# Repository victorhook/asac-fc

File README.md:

# ASAC FC

**A** **S**imple **A**nd **C**ool **F**light **C**ontroller (**ASAC FC**) is a completely open-source flight controller that can run on multiple microcontrollers such as:
- rp2040
- rp2350

## Project goals
- [ ] Build a drone with rp2040 devboard + external IMU
- [ ] Build a drone with rp2350 devboard + external IMU
- [ ] Add Stabilize flight mode
- [ ] Add Althold flight mode (requires barometer)
- [ ] Add support for SD card logging
- [ ] UI To configure board
- [X] Separate HAL to build for different platforms (rp2040, sitl etc)

What should be configurable, and what should be built-in to firmware?
### Built-in
Must still be able to boot OK without any of these

### Configurable
- Barometer
- IMU
- RC receiver
- Motor order
- FC orientation

---

TODO: THIS GIF [ASAC Takeoff](docs/asac_takeoff.gif)

## Why rp2040?
It's an incredibly cheap microcontroller that is quite powerful (up to 133 MHz), contains two cores, programmable I/O pins (PIO), seems to ignore the global silicon shortage and has an extensive C/C++ SDK.

## Iteration 2

For the second iteration of the flight controller I designed a PCB in FreeCad, ordered the pcb and components with SMD assembly for the top layer, and soldered the bottom layer myself. All cad files of this can be found in [kicad/asac-fc-rev-b](kicad/asac-fc-rev-b). Schematic can also be found at [documents/asac-fc-rev-b.pdf](documents/asac-fc-rev-b.pdf).
Some nice features of the flight controller PCB are:

- **rp2040** - Flight controller (where asac runs)
- **BMI270** - IMU, using SPI, which allows faster readings than the MPU-6050 which was used for iteration 1.
- **USB-C** - More modern, right? :)
- **Individual ESC solder pads** - Connection for individual ESCs. While most flight stacks today use an 4-in-1 ESC, I decided to keep it simple and use individual ESCs for now.
- **Battery solder pads**

## Iteration 1

The first iteration of *asac fc* was done with development boards, before designing a custom PCB. This is to make a proof of concept, and serves as a sanity check to show that it's possible :). The main components are:
- **Raspberry pi pico** - Flight controller (where asac runs)
- **MPU6050** - IMU
- **FS-a8s** - Radio receiver (Flysky, outputs IBUS)
- **xsd7a ESC** - ESCs (Single motor ESCs, so 4 in total)
- **Frame** - Custom designed, 3D-printed in PLA.

I created a simple power distribution board (brown part, at the bottom of the drone in the picture below), where the battery is connected to. Each ESC as well as the pico and the receiver gets its power from this board. The ESCs are then connected to GPIOs on the pico.

After some manual (headless) flights, I decided to add an analog camera together with a VTX I had laying around. This way, we can fly some FPV with the pico!

## Features

### Sensors
- [X] IMU
- [ ] GPS
- [ ] Barometer (altitude estimation)
- [ ] Lidar or other distance sensor

### Receiver protocols
- [X] IBUS
- [ ] SBUS
- [ ] Frsky
- [ ] CSRF

### Telemetry
- [ ] Any

### Flight modes
- [X] Acro (attitude rate, aka free-style)
- [ ] Any other stabilizing mode

### ESC Protocols

- [X] PWM (50 hz)
- [X] Oneshot125, utilizing rp2040s PIO block
- [X] Oneshot42, utilizing rp2040s PIO block
- [ ] Multishot
- [ ] Dshot150
- [ ] Dshot300
- [ ] Dshot600
- [ ] Dshot1200
- [ ] ProShot

## From receiver input to motor outputs

In order to set the correct speeds for each motor, several steps must be taken. The steps described below is how it's done for *asac fc*. Note that this is for acro mode only (freestyle, using only gyro rates from IMU).

1. Read gyro rates from IMU
2. Remove bias from gyro reading
3. Filter gyro reading
4. Read receiver input
5. Convert receiver stick inputs to desired gyro rates. This is a mapping from eg. 1000-2000 -> -500 to 500 deg/s.
6. Give the *desired* rates together with the *measured* rates to PID controller that uses PID parameters to calculate adjustment values.
7. Give output from PID controller to motor mixer to get commands for each motor.
8. Send the motor outputs to the ESC(s).

## RTOS
*asac fc* uses a very simple RTOS called [vsrtos](https://github.com/victorhook/vsrtos), that uses a priority based non-preemptive scheduling technique to run tasks. While this rtos is quite immature, it works just fine for this application, since *asac fc* doesn't have that many tasks yet.

## Motor mixing

The motor mixer is responsible for deciding which motor should spin and how much. *asac fc* uses the default motor numbers like in the image below, which is the same as the default for betaflight.

The default motor mix is:

| Motor | Throttle | Roll | Pitch | Yaw |
| --- | --- | --- | --- | --- |
| 1 | 1 | -1 | 1  | -1 |
| 2 | 1 | -1 | -1 | 1  |
| 3 | 1 | 1  | 1  | 1 |
| 4 | 1 | 1  | -1 | -1  |

## Flashing

You can flash the pico through in three different ways:
1. Through USB, when it's connected as a USB device (press down button while powering the pico)
2. Through serial USB by utilizing the picotool:
   `picotool load -f target.uf2 && picotool reboot -f`
    This works if uart 0 is mapped to USB:
    ```
    pico_enable_stdio_uart(asac-fc 0)
    pico_enable_stdio_usb(asac-fc 1)
    ```
    The command above first flashes the target `uf2` file to the pico by forcing it into BOOTSEL mode. We then reset the pico with `picotool reboot -f`. The flag `-f` is crucial here, since it allows us to load and reboot it without being in BOOTSEL mode already. I think it accomplishes this by changing the baud rate of the connection, which forces the pico to BOOTSEL mode, but I am not 100% sure.
3. SWD using debugger/another pico.

## Available build defines

There are several parameters that can be defined on build-time to configure the firmware. All of the defines can also be found in the `CMakeLists.txt` These includes:

| Define | Description |
| --- | --- |
| USE_DEFAULT_SETTINGS | If defined, asac will use default settings and write them to flash. Note that this will erase any previous settings that were stored in flash. This can be useful when using the flight controller for the first time, or updating the data structure of the flash. |
| LINUX | If defined, the firmware is built to be run on a linux machine and *not* for rp2040. This can be useful if you want to run unit tests on certain parts of code, or simulate fc. |
| RP2040 | Used by vsrtos. Do not change |

## Resources
- [Embedded Programming for Quadcopters](https://www.youtube.com/watch?v=CHSYgLfhwUo&ab_channel=Code%26Supply)
- [Motor mixing](https://oscarliang.com/custom-motor-output-mix-quadcopter/)

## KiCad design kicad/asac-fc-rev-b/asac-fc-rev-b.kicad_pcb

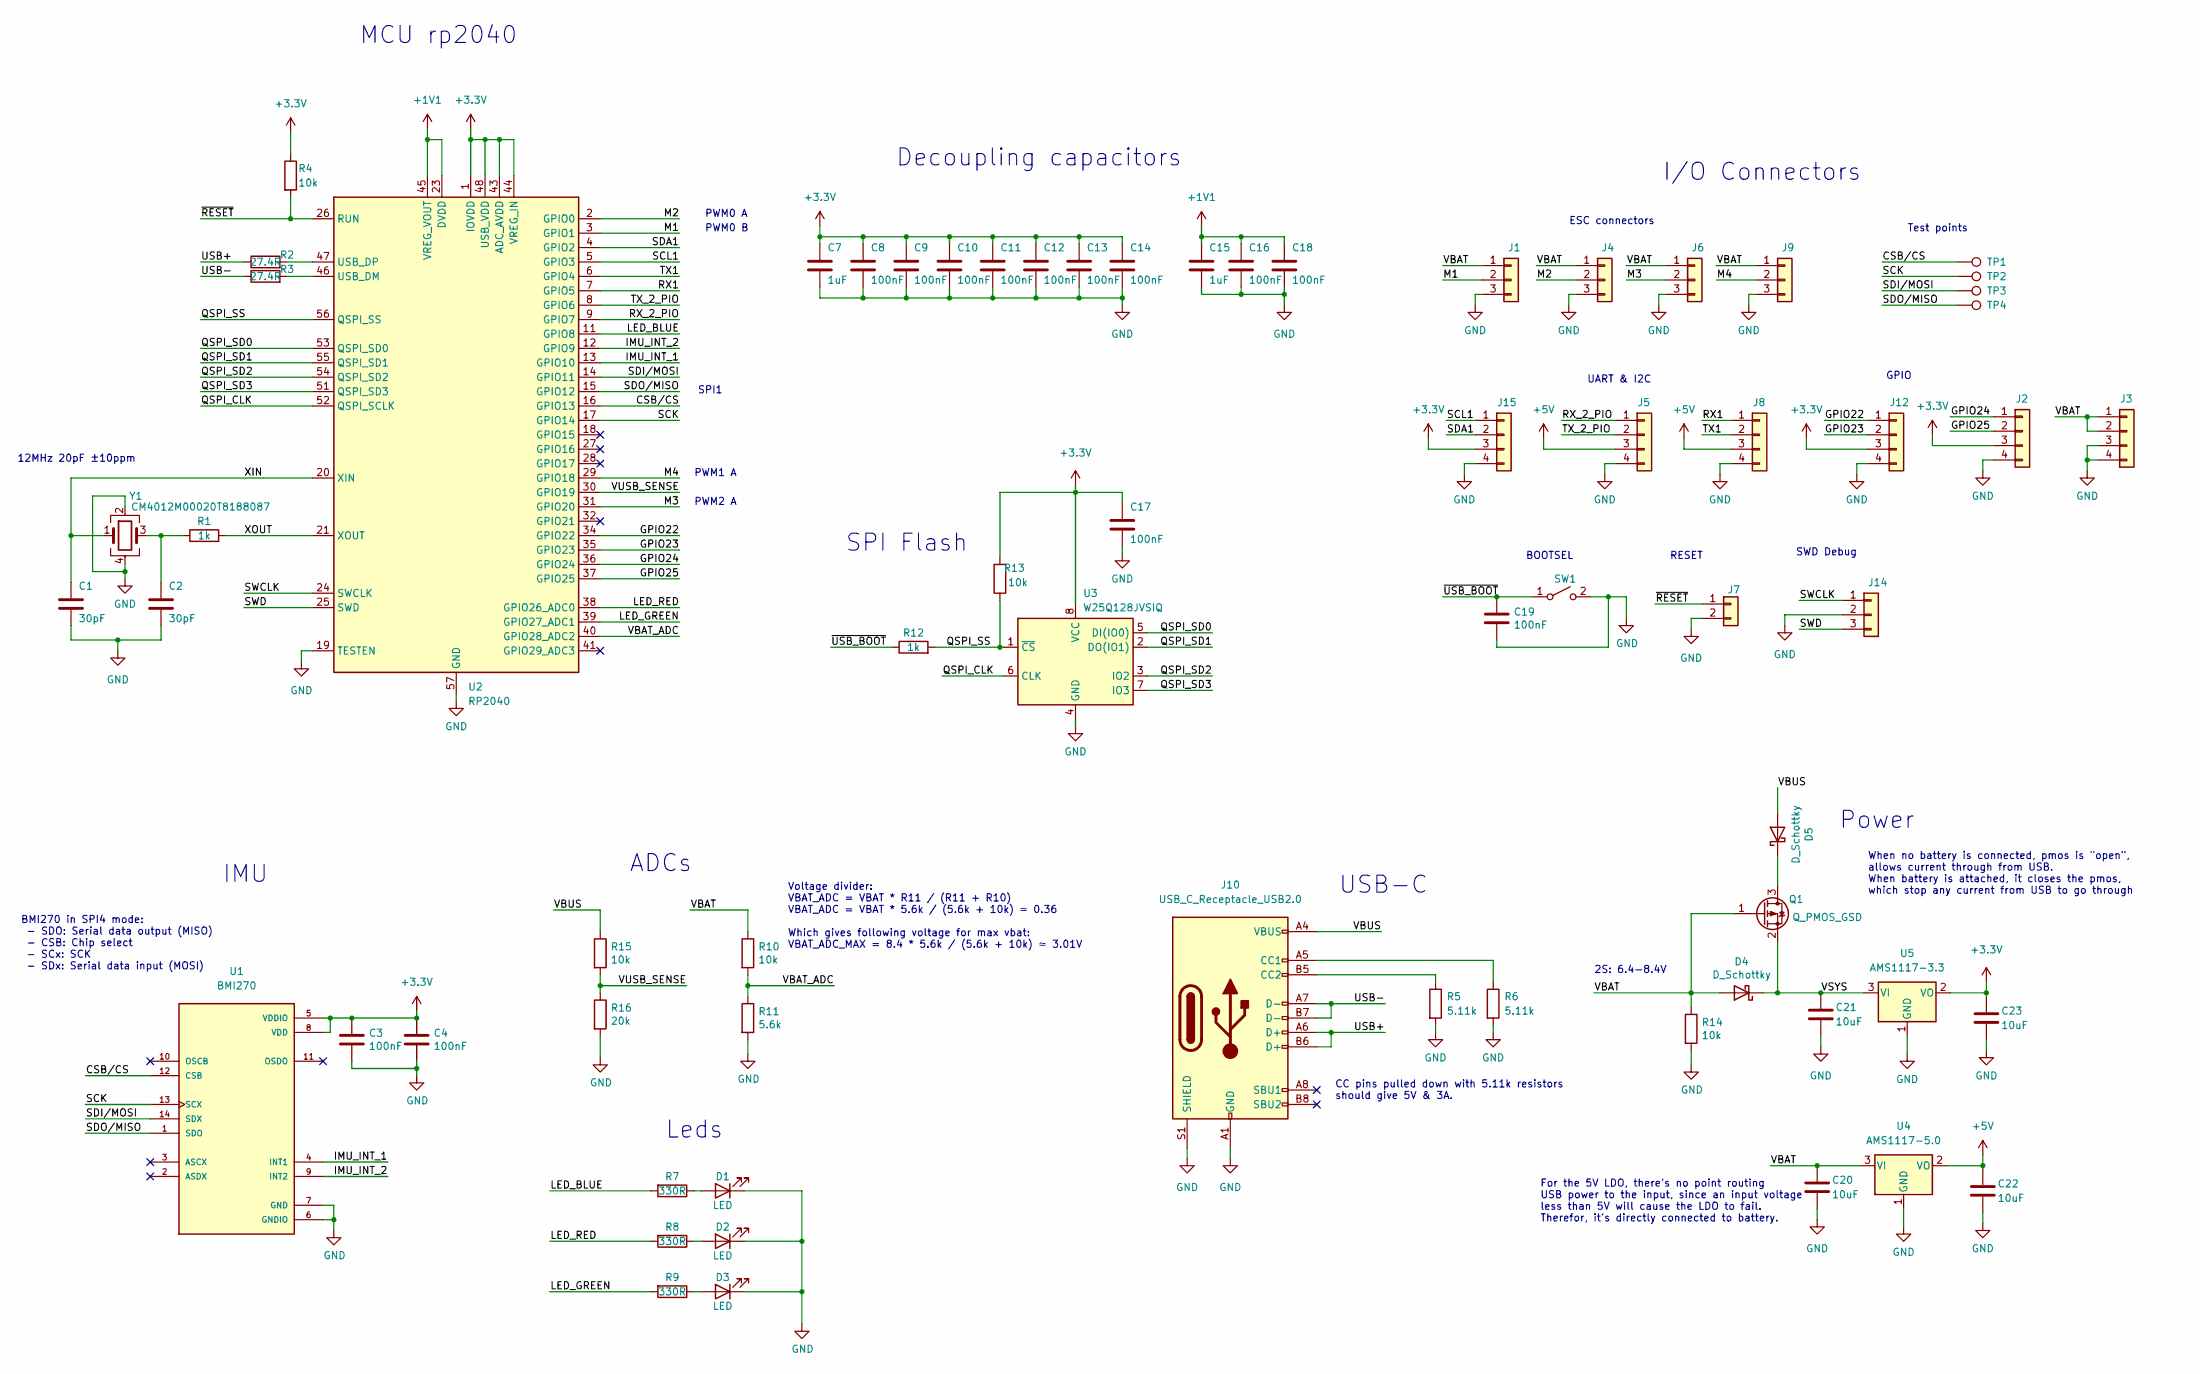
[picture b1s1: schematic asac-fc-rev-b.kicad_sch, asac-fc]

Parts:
C1, C2: 30pF; C_0402_1005Metric
C3, C4, C8, C9, C10, C11, C12, C13, C14, C16, C17, C18, C19: 100nF; C_0402_1005Metric
C7, C15: 1uF; C_0402_1005Metric
C20, C21, C22, C23: 10uF; C_0805_2012Metric
D1, D2, D3: LED; LED_0603_no_outline
D4, D5: D_Schottky; D_SOD-123
J1, J4, J6, J9: Conn_01x03; Conn_01x03_2big_1small
J2, J3, J5, J8, J12, J15: Conn_01x04; Conn_01x04_fpv
J7: Conn_01x02; Conn_01x02_small
J10: USB_C_Receptacle_USB2.0; USB-SMD_GT-USB-7010AN
J14: Conn_01x03; PinHeader_1x03_P1.27mm_Vertical_no_silk_smd
Q1: Q_PMOS_GSD; SOT-23
R1, R12: 1k; R_0402_1005Metric
R2, R3: 27.4R; R_0402_1005Metric
R4, R10, R13, R14, R15: 10k; R_0402_1005Metric
R5, R6: 5.11k; R_0402_1005Metric
R7, R8, R9: 330R; R_0402_1005Metric
R11: 5.6k; R_0402_1005Metric
R16: 20k; R_0402_1005Metric
SW1: SW_SPST; SW-SMD_TS-1086EV-16
TP1, TP2, TP3, TP4: TestPoint; TP_0.7mm
U1: BMI270
U2: RP2040; QFN-56-1EP_7x7mm_P0.4mm_EP3.2x3.2mm
U3: W25Q128JVSIQ; SOIC-8_5.23x5.23mm_P1.27mm
U4: AMS1117-5.0; SOT-223-3_TabPin2
U5: AMS1117-3.3; SOT-223-3_TabPin2
Y1: CM4012M00020T8188087; Crystal_SMD_2520-4Pin_2.5x2.0mm

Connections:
+1V1: C15.1, C16.1, C18.1, U2.23 (DVDD), U2.45 (VREG_VOUT), U2.50 (DVDD)
+3.3V: C3.1, C4.1, C7.1, C8.1, C9.1, C10.1, C11.1, C12.1, C13.1, C14.1, C17.1, C23.1, J2.3, J12.3, J15.3, R4.1, R13.2, U1.5 (VDDIO), U1.8 (VDD), U2.1 (IOVDD), U2.10 (IOVDD), U2.22 (IOVDD), U2.33 (IOVDD), U2.42 (IOVDD), U2.43 (ADC_AVDD), U2.44 (VREG_IN), U2.48 (USB_VDD), U2.49 (IOVDD), U3.8 (VCC), U5.2 (VO)
+5V: C22.1, J5.3, J8.3, U4.2 (VO)
/CSB/CS: TP1.1, U1.12 (CSB), U2.16 (GPIO13)
/GPIO22: J12.1, U2.34 (GPIO22)
/GPIO23: J12.2, U2.35 (GPIO23)
/GPIO24: J2.1, U2.36 (GPIO24)
/GPIO25: J2.2, U2.37 (GPIO25)
/IMU_INT_1: U1.4 (INT1), U2.13 (GPIO10)
/IMU_INT_2: U1.9 (INT2), U2.12 (GPIO9)
/LED_BLUE: R7.2, U2.11 (GPIO8)
/LED_GREEN: R9.2, U2.39 (GPIO27_ADC1)
/LED_RED: R8.2, U2.38 (GPIO26_ADC0)
/M1: J1.2, U2.3 (GPIO1)
/M2: J4.2, U2.2 (GPIO0)
/M3: J6.2, U2.31 (GPIO20)
/M4: J9.2, U2.29 (GPIO18)
/QSPI_CLK: U2.52 (QSPI_SCLK), U3.6 (CLK)
/QSPI_SD0: U2.53 (QSPI_SD0), U3.5 (DI(IO0))
/QSPI_SD1: U2.55 (QSPI_SD1), U3.2 (DO(IO1))
/QSPI_SD2: U2.54 (QSPI_SD2), U3.3 (IO2)
/QSPI_SD3: U2.51 (QSPI_SD3), U3.7 (IO3)
/QSPI_SS: R12.2, R13.1, U2.56 (QSPI_SS), U3.1 (~CS)
/RX1: J8.1, U2.7 (GPIO5)
/RX_2_PIO: J5.1, U2.9 (GPIO7)
/SCK: TP2.1, U1.13 (SCX), U2.17 (GPIO14)
/SCL1: J15.1, U2.5 (GPIO3)
/SDA1: J15.2, U2.4 (GPIO2)
/SDI/MOSI: TP3.1, U1.14 (SDX), U2.14 (GPIO11)
/SDO/MISO: TP4.1, U1.1 (SDO), U2.15 (GPIO12)
/SWCLK: J14.1, U2.24 (SWCLK)
/SWD: J14.3, U2.25 (SWD)
/TX1: J8.2, U2.6 (GPIO4)
/TX_2_PIO: J5.2, U2.8 (GPIO6)
/USB+: J10.A6 (D+), J10.B6 (D+), R2.1
/USB-: J10.A7 (D-), J10.B7 (D-), R3.1
/VBAT: C20.1, D4.2 (A), J1.1, J3.1, J3.2, J4.1, J6.1, J9.1, Q1.1 (G), R10.1, R14.1, U4.3 (VI)
/VBAT_ADC: R10.2, R11.1, U2.40 (GPIO28_ADC2)
/VBUS: D5.2 (A), J10.A4 (VBUS), J10.A9 (VBUS), J10.B4 (VBUS), J10.B9 (VBUS), R15.1
/VSYS: C21.1, D4.1 (K), Q1.2 (S), U5.3 (VI)
/VUSB_SENSE: R15.2, R16.1, U2.30 (GPIO19)
/XIN: C1.1, U2.20 (XIN), Y1.1
/XOUT: R1.2, U2.21 (XOUT)
/~RESET: J7.1, R4.2, U2.26 (RUN)
/~USB_BOOT: C19.1, R12.1, SW1.1 (A)
GND: C1.2, C2.2, C3.2, C4.2, C7.2, C8.2, C9.2, C10.2, C11.2, C12.2, C13.2, C14.2, C15.2, C16.2, C17.2, C18.2, C19.2, C20.2, C21.2, C22.2, C23.2, D1.1 (K), D2.1 (K), D3.1 (K), J1.3, J2.4, J3.3, J3.4, J4.3, J5.4, J6.3, J7.2, J8.4, J9.3, J10.A1 (GND), J10.A12 (GND), J10.B1 (GND), J10.B12 (GND), J10.S1 (SHIELD), J12.4, J14.2, J15.4, R5.2, R6.2, R11.2, R14.2, R16.2, SW1.2 (B), U1.6 (GNDIO), U1.7 (GND), U2.19 (TESTEN), U2.57 (GND), U3.4 (GND), U4.1 (GND), U5.1 (GND), Y1.2, Y1.4
unnamed: C2.1, R1.1, Y1.3
unnamed: D1.2 (A), R7.1
unnamed: D2.2 (A), R8.1
unnamed: D3.2 (A), R9.1
unnamed: D5.1 (K), Q1.3 (D)
unnamed: J10.A5 (CC1), R6.1
unnamed: J10.B5 (CC2), R5.1
unnamed: R2.2, U2.47 (USB_DP)
unnamed: R3.2, U2.46 (USB_DM)

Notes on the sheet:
Power
2S: 6.4-8.4V
MCU rp2040
BOOTSEL
Leds
UART & I2C
CC pins pulled down with 5.11k resistors should give 5V & 3A.
12MHz 20pF ±10ppm
PWM2 A
SPI Flash
SWD Debug
Test points
USB-C
ESC connectors
When no battery is connected, pmos is "open", allows current through from USB. When battery is attached, it closes the pmos, which stop any current from USB to go through
PWM1 A
Voltage divider: VBAT_ADC = VBAT * R11 / (R11 + R10) VBAT_ADC = VBAT * 5.6k / (5.6k + 10k) ≃ 0.36 Which gives following voltage for max vbat: VBAT_ADC_MAX = 8.4 * 5.6k / (5.6k + 10k) ≃ 3.01V
Decoupling capacitors
I/O Connectors
PWM0 A
SPI1
PWM0 B
For the 5V LDO, there's no point routing USB power to the input, since an input voltage less than 5V will cause the LDO to fail. Therefor, it's directly connected to battery.
BMI270 in SPI4 mode: - SDO: Serial data output (MISO) - CSB: Chip select - SCx: SCK - SDx: Serial data input (MOSI)
ADCs
GPIO
RESET
IMU

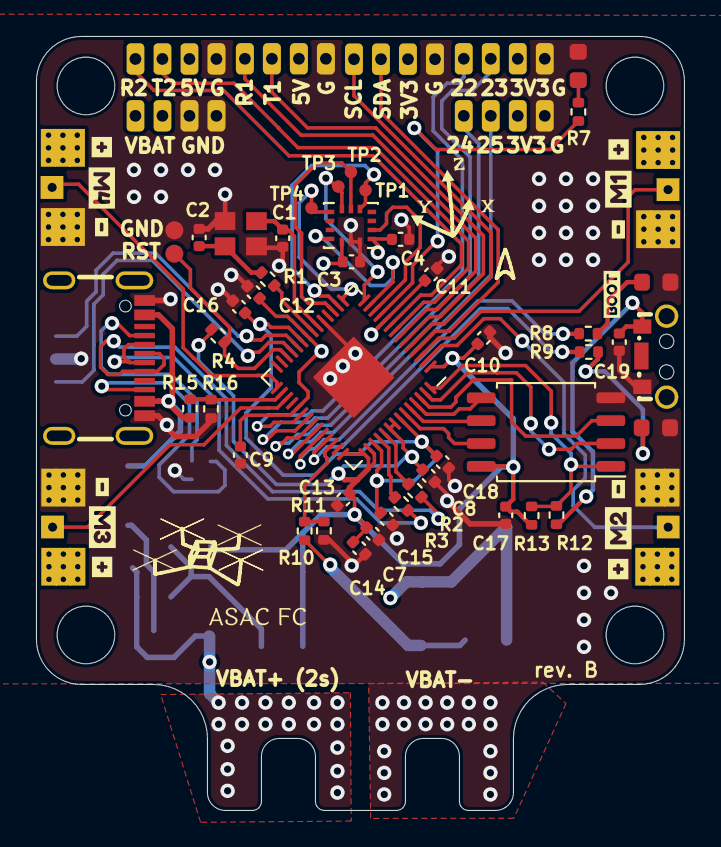
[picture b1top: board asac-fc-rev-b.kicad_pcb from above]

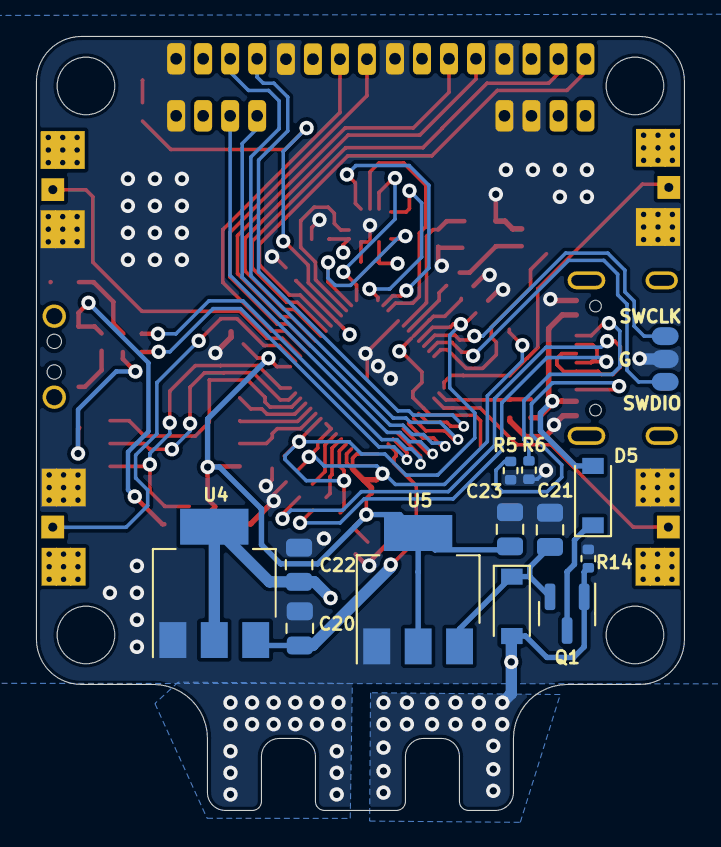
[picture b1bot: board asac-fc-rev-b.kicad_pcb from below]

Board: 4 copper layers, 36.0 x 43.0 mm, 80 parts (13 on the bottom side), 55 nets.

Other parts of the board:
kibuzzard-647F08DD, kibuzzard-647F08DD#2: G***; kibuzzard-647F08DD
kibuzzard-647F08EC, kibuzzard-647F08EC#2: G***; kibuzzard-647F08EC
kibuzzard-647F08F4: G***; kibuzzard-647F08F4
kibuzzard-647F09B6: G***; kibuzzard-647F09B6
kibuzzard-647F09BC: G***; kibuzzard-647F09BC
kibuzzard-647F096A, kibuzzard-647F096A#2: G***; kibuzzard-647F096A
kibuzzard-647F0963: G***; kibuzzard-647F0963
kibuzzard-647F0971, kibuzzard-647F0971#2: G***; kibuzzard-647F0971
kibuzzard-640905D0: G***; kibuzzard-640905D0

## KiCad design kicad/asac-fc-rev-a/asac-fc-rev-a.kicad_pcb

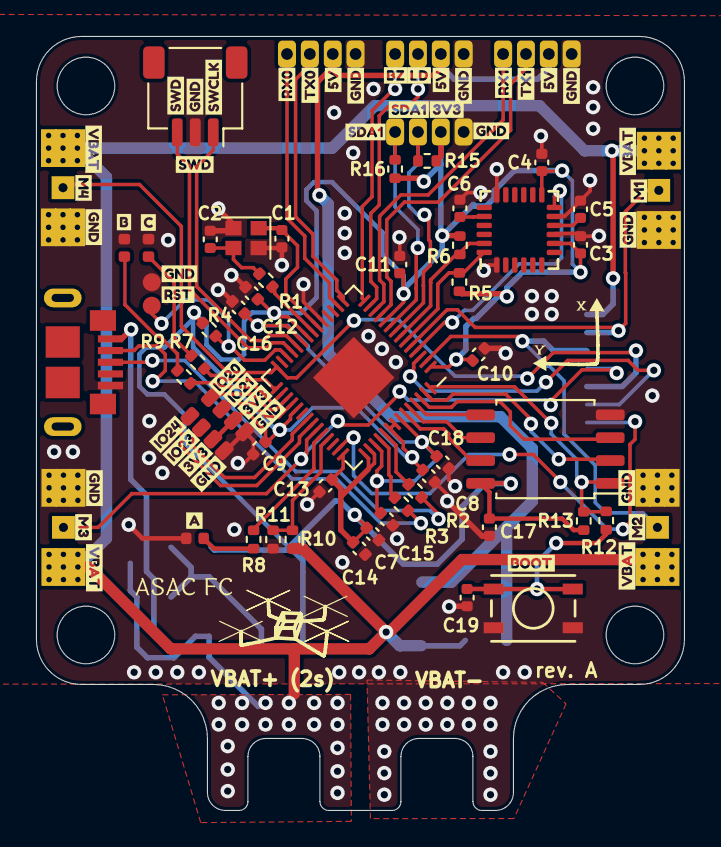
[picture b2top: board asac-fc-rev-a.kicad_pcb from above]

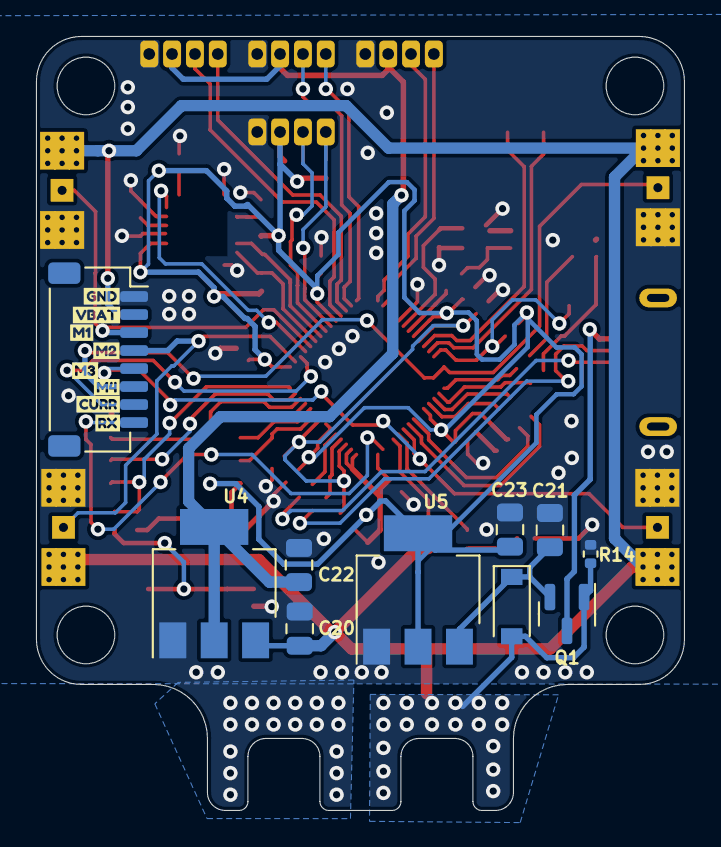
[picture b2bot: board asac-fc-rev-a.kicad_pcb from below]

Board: 2 copper layers, 36.0 x 43.0 mm, 119 parts (18 on the bottom side), 54 nets.

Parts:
C1, C2: 7pF; C_0402_1005Metric
C3, C4, C5, C8, C9, C10, C11, C12, C13, C14, C16, C17, C18: 0.1uF; C_0402_1005Metric
C6: 2.2nF; C_0402_1005Metric
C7, C15: 1uF; C_0402_1005Metric
C19: 100nF; C_0402_1005Metric
C20, C21, C22, C23: 10uF; C_0805_2012Metric
D1, D2, D3: LED; LED_0402_1005Metric_No_silk_dot
D4: D_Schottky; D_SOD-123
J1, J4, J6, J9: Conn_01x03; Conn_01x03_2big_1small
J2, J12: Conn_01x04; Conn_01x04_fpv_smd
J3: USB3075-30-A; USB3075-30-A_No_silk
J5, J8, J10, J15: Conn_01x04; Conn_01x04_fpv
J7: Conn_01x02; Conn_01x02_small
J11: Conn_01x08; JST_SH_SM08B-SRSS-TB_1x08-1MP_P1.00mm_Horizontal
J14: Conn_01x03; JST_SH_SM03B-SRSS-TB_1x03-1MP_P1.00mm_Horizontal
Q1: Q_PMOS_GSD; SOT-23
R1, R12: 1k; R_0402_1005Metric
R2, R3: 27.4; R_0402_1005Metric
R4, R10, R13, R14: 10k; R_0402_1005Metric
R5, R6, R15, R16: 2.2k; R_0402_1005Metric
R7, R8, R9: 330; R_0402_1005Metric
R11: 5.6k; R_0402_1005Metric
SW1: BOOT; PTS815
U1: MPU-6050; InvenSense_QFN-24_4x4mm_P0.5mm
U2: RP2040; QFN-56-1EP_7x7mm_P0.4mm_EP3.2x3.2mm
U3: W25Q128JVS; SOIC-8_5.23x5.23mm_P1.27mm
U4: AMS1117-5.0; SOT-223-3_TabPin2
U5: AMS1117-3.3; SOT-223-3_TabPin2
Y1: Crystal_GND24; Crystal_SMD_2016-4Pin_2.0x1.6mm
kibuzzard-6408FA6D, kibuzzard-6408FA6D#2, kibuzzard-6408FA6D#3, kibuzzard-6408FA6D#4: G***; kibuzzard-6408FA6D
kibuzzard-6408FA39: G***; kibuzzard-6408FA39
kibuzzard-6408FA47: G***; kibuzzard-6408FA47
kibuzzard-6408FA74, kibuzzard-6408FA74#2, kibuzzard-6408FA74#3: G***; kibuzzard-6408FA74
kibuzzard-6408FAC1: G***; kibuzzard-6408FAC1
kibuzzard-6408FAC8: G***; kibuzzard-6408FAC8
kibuzzard-6408FB3B: G***; kibuzzard-6408FB3B
kibuzzard-6408FB51: G***; kibuzzard-6408FB51
kibuzzard-6408FBAE: G***; kibuzzard-6408FBAE
kibuzzard-6408FBBA: G***; kibuzzard-6408FBBA
kibuzzard-6408FC3B: G***; kibuzzard-6408FC3B
kibuzzard-6408FC28: G***; kibuzzard-6408FC28
kibuzzard-6408FC36: G***; kibuzzard-6408FC36
kibuzzard-6408FC56: G***; kibuzzard-6408FC56
kibuzzard-6408FD3E, kibuzzard-6408FD3E#2, kibuzzard-6408FD3E#3, kibuzzard-6408FD3E#4: G***; kibuzzard-6408FD3E
kibuzzard-6408FD16: G***; kibuzzard-6408FD16
kibuzzard-6408FD22, kibuzzard-6408FD22#2, kibuzzard-6408FD22#3, kibuzzard-6408FD22#4: G***; kibuzzard-6408FD22
kibuzzard-6408FDA0: G***; kibuzzard-6408FDA0
kibuzzard-6408FDC2: G***; kibuzzard-6408FDC2
kibuzzard-6408FDE1: G***; kibuzzard-6408FDE1
kibuzzard-64090C7A: G***; kibuzzard-64090C7A
kibuzzard-64090F7E: G***; kibuzzard-64090F7E
kibuzzard-64090F8A: G***; kibuzzard-64090F8A
kibuzzard-64090F8F: G***; kibuzzard-64090F8F
kibuzzard-64090F9C: G***; kibuzzard-64090F9C
kibuzzard-64090F56: G***; kibuzzard-64090F56
kibuzzard-64090F66: G***; kibuzzard-64090F66
kibuzzard-64090F74: G***; kibuzzard-64090F74
kibuzzard-64090F95: G***; kibuzzard-64090F95
kibuzzard-640900D1: G***; kibuzzard-640900D1
kibuzzard-640901D1: G***; kibuzzard-640901D1
kibuzzard-640901E3: G***; kibuzzard-640901E3
kibuzzard-640905D0: G***; kibuzzard-640905D0
kibuzzard-640910AE, kibuzzard-640910AE#2: G***; kibuzzard-640910AE
kibuzzard-640910C2: G***; kibuzzard-640910C2
kibuzzard-640911E9: G***; kibuzzard-640911E9
kibuzzard-640911EE: G***; kibuzzard-640911EE
kibuzzard-6409014C: G***; kibuzzard-6409014C
kibuzzard-6409115F: G***; kibuzzard-6409115F
kibuzzard-64090145: G***; kibuzzard-64090145
kibuzzard-64091195, kibuzzard-64091195#2: G***; kibuzzard-64091195

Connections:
+1V1: C15.1, C16.1, C18.1, U2.23 (DVDD), U2.45 (VREG_VOUT), U2.50 (DVDD)
+3.3V: C3.1, C4.1, C7.1, C8.1, C9.1, C10.1, C11.1, C12.1, C13.1, C14.1, C17.1, C23.1, J2.3, J12.3, J15.3, R4.1, R5.1, R6.1, R13.2, R15.1, R16.1, U1.8 (VDDIO), U1.13 (VDD), U2.1 (IOVDD), U2.10 (IOVDD), U2.22 (IOVDD), U2.33 (IOVDD), U2.42 (IOVDD), U2.43 (ADC_AVDD), U2.44 (VREG_IN), U2.48 (USB_VDD), U2.49 (IOVDD), U3.8 (VCC), U5.2 (VO)
+5V: C22.1, J5.3, J8.3, J10.3, U4.2 (VO)
/BUZZER: J10.1, U2.14 (GPIO11)
/CURR: J11.7, U2.3 (GPIO1)
/GPIO20: J12.1, U2.31 (GPIO20)
/GPIO21: J12.2, U2.32 (GPIO21)
/GPIO23: J2.2, U2.35 (GPIO23)
/GPIO24: J2.1, U2.36 (GPIO24)
/IMU_INTERRUPT: U1.12 (INT), U2.4 (GPIO2)
/LED: J10.2, U2.13 (GPIO10)
/LED_BLUE: R7.2, U2.29 (GPIO18)
/LED_GREEN: R9.2, U2.30 (GPIO19)
/LED_RED: R8.2, U2.38 (GPIO26_ADC0)
/M1: J1.2, J11.3, U2.5 (GPIO3)
/M2: J4.2, J11.4, U2.2 (GPIO0)
/M3: J6.2, J11.5, U2.37 (GPIO25)
/M4: J9.2, J11.6, U2.28 (GPIO17)
/QSPI_CLK: U2.52 (QSPI_SCLK), U3.6 (CLK)
/QSPI_SD0: U2.53 (QSPI_SD0), U3.5 (DI(IO0))
/QSPI_SD1: U2.55 (QSPI_SD1), U3.2 (DO(IO1))
/QSPI_SD2: U2.54 (QSPI_SD2), U3.3 (IO2)
/QSPI_SD3: U2.51 (QSPI_SD3), U3.7 (IO3)
/QSPI_SS: R12.2, R13.1, U2.56 (QSPI_SS), U3.1 (~CS)
/RX0: J5.1, U2.16 (GPIO13)
/RX1: J8.1, U2.12 (GPIO9)
/RX_ESC: J11.8, U2.41 (GPIO29_ADC3)
/SCL0: R6.2, U1.23 (SCL), U2.7 (GPIO5)
/SCL1: J15.1, R16.2, U2.9 (GPIO7)
/SDA0: R5.2, U1.24 (SDA), U2.6 (GPIO4)
/SDA1: J15.2, R15.2, U2.8 (GPIO6)
/SWCLK: J14.1, U2.24 (SWCLK)
/SWD: J14.3, U2.25 (SWD)
/TX0: J5.2, U2.15 (GPIO12)
/TX1: J8.2, U2.11 (GPIO8)
/USB+: J3.3 (D+), R2.1
/USB-: J3.2 (D-), R3.1
/VBAT: C20.1, D4.2 (A), J1.1, J4.1, J6.1, J9.1, J11.2, Q1.1 (G), R10.1, R14.1, U4.3 (VI)
/VBAT_ADC: R10.2, R11.1, U2.39 (GPIO27_ADC1)
/VBUS: J3.1 (VBUS), Q1.3 (D)
/XIN: C1.1, U2.20 (XIN), Y1.1
/XOUT: R1.2, U2.21 (XOUT)
/~RESET: J7.1, R4.2, U2.26 (RUN)
/~USB_BOOT: C19.1, R12.1, SW1.1, SW1.2
GND: C1.2, C2.2, C3.2, C4.2, C5.2, C6.2, C7.2, C8.2, C9.2, C10.2, C11.2, C12.2, C13.2, C14.2, C15.2, C16.2, C17.2, C18.2, C19.2, C20.2, C21.2, C22.2, C23.2, D1.1 (K), D2.1 (K), D3.1 (K), J1.3, J2.4, J3.5 (GND), J4.3, J5.4, J6.3, J7.2, J8.4, J9.3, J10.4, J11.1, J12.4, J14.2, J15.4, R11.2, R14.2, SW1.3 (K), SW1.4 (A), U1.1 (CLKIN), U1.9 (AD0), U1.11 (FSYNC), U1.18 (GND), U2.19 (TESTEN), U2.57 (GND), U3.4 (GND), U4.1 (GND), U5.1 (GND), Y1.2, Y1.4
unnamed: C2.1, R1.1, Y1.3
unnamed: C5.1, U1.10 (REGOUT)
unnamed: C6.1, U1.20 (CPOUT)
unnamed: C21.1, D4.1 (K), Q1.2 (S), U5.3 (VI)
unnamed: D1.2 (A), R7.1
unnamed: D2.2 (A), R8.1
unnamed: D3.2 (A), R9.1
unnamed: R2.2, U2.47 (USB_DP)
unnamed: R3.2, U2.46 (USB_DM)

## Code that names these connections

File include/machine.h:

#ifndef MACHINE_H
#define MACHINE_H


// Pin definitions for custom PCB - Revision B
// TODO: Incorrect motor names!!
// Motor MIXER M1 and M2 are swapped. The motor mixer uses betaflights
// motor mix!
// M1 in schematic and PCB is actually M2 according to motor mixer :)
// So M1 and M2 are swapped
//#define PIN_M1                 1
//#define PIN_M2                 0
#define PIN_M3                20
#define PIN_M4                18
#define PIN_M1                 0
#define PIN_M2                 1

#define PIN_VBAT_ADC          28
#define VBAT_ADC_INPUT_NUMBER  2

#define PIN_IMU_MOSI          11
#define PIN_IMU_MISO          12
#define PIN_IMU_CS            13
#define PIN_IMU_SCK           14
#define PIN_IMU_INTERRUPT_1   10
#define PIN_IMU_INTERRUPT_2    9
#define IMU_SPI_BUS           spi1

#define PIN_VUSB_SENSE        19

#define PIN_SDA1               2
#define PIN_SCL1               3

#define PIN_TX1                4
#define PIN_RX1                5
#define PIN_TX2_PIO            6
#define PIN_RX2_PIO            7

#define PIN_LED_BLUE           8
#define PIN_LED_GREEN          27
#define PIN_LED_RED            26

#define PIN_TELEMETRY_TX 0

// 16 MB
#define ASAC_FC_FLASH_SIZE        (16 * 1024 * 1024)


#endif

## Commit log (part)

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2023-03-10 Added first blog post (not done yet)
2023-03-15 - Created some base source code files. - Added cmake file to build. - Added vscode config files for intellisense etc.
2023-03-15 Added some datasheets
2023-03-15 Created and added rough start of some random tools
2023-03-27 Added some 3d models
2023-03-27 Added kicad pcb
2023-03-28 Modified vscode settings to make debugging with SWD work.
2023-03-30 - Added logic to motor mixer - Added init method for pid-controller - Added more logic to controller_update() (PID-loop main function)
2023-04-01 - Some general cleanup - Change motor API, - Added arm state - Added connected state - First (unstable) takeoff done!
2023-04-05 - Made controller variables public - Made PID variables public - Added debug pwm pin to motors - Changed type pid params to floats - Added timeout on i2c reading for mpu driver
2023-05-04 Started working on a gui to plot and display logging telemetry parameters
2023-05-06 - Added logic for handling states (log blocks) - Extended backend to fetch from actual flask server
2023-05-27 - Added packed attribute to log structs - Configured telemetry module and made it work. This was implemented with pio UART, seems to work pretty well, even with 921600 baudrate. - Added while loop to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
2023-05-28 - Added timer functions to asac_fc and fixed bug in them - Added data integrity protection to ibus module, by inspecting and validating the checksum. Also improved the state machine of the module. - 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
2023-05-31 First controlled take-off and flight, wehooo!! - Found CRUICAL reason why drone spun onctrollably around yaw axis, the Z from IMU was expected to be pointing DOWN according the the PID controller, bu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
2023-05-31 Some minor cleanup for most files
2023-06-04 - Removed reading acc data from imu to save reading time. - Cleaned up control update function. - Tuned PID params after flying, increased quite a bit - Made TELEMETRY_LOGGING define to enable/disabl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
2023-06-04 Improved README.md
2023-06-11 Added oneshot PIO implementation. This utilizes the entire PIO1 block to send oneshot pulses to the motors. A great benefit of this is that the main processor doesn't have to do anything except for t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
2023-06-11 Changed to oneshot42
2023-06-14 Some general cleanup - Created separate folder in cad directory - Added README.md for each directory - Added some description for makefile targets
2023-06-20 Started on migration to support PCB rev. B - Added BMI270 Sensor API submodule, and wrote a wrapper around it to make it use rp2040s SPI drivers. Seems to work OK! - Changed PIN definitions in "machi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
2023-06-28 Changed debug print every sec check to #ifdef for vsrtos
2023-06-29 Initial MAVlink integration
    - Decided to try out MAVlink so in this commit I have integrated a first
    part of MAVlink protocol on ASAC. Initially I thought of creating a
    custom dialect, but think I will go for a common one instead, we'll
    see.
    - Added mavlink C headers
    - Created python serial client that uses pymavlink to parse the data.
2023-07-05 Parameter setting and saving to flash
    - Fixed parameter setting through MAVlink
    - Added support for MAVlink command to write
    parameters to permanent storage (flash)
    - Added support for MAVlink reboot command
2023-07-18 Added some info about new pcb and updated README git some images. Also exported schematic as PDF.
2023-08-27 Changed default PID settings
2023-08-27 Created option to run firmware on linux
    In order to aid development, it would be nice to run
    certain pieces of code on a normal linux machine. For instance
    if we want to run unit tests or simulations. For this, I created a
    define, "LINUX" which (if defined) should make the firmware
    possible to run on linux instead of rp2040.
2023-08-27 Added initial CRSF and refactored receiver code
    - Added initial support for CRSF. This commit only includes reading
    CRFS frames, and so far only channel data and link statistics frames
    are parsed.
    - Moved ibus & crsf into separate rc directory, with a "generic"
    rc file "rc.h". The idea here is that each RC protocol should be
    able to fill an `rx_state_t` with correct information.
2023-08-27 Update info about build defines
    Added some info in `README.md` regarding build
    defines and their usage.
2023-08-27 Serial mavlink refactorization
    - Cleaned up a bit in the serial mavlink handler.
    - Added check for USB voltage before trying to send/read any data
    through the serial port. This is added because if we're not connected
    to USB, there's no point to try to read data, nor send anything.
    - Created 1 single task for all mavlink communication instead of
    separate ones. Inside this task the timing for periodic messages
2023-09-06 Added param print to main and some cleanup
    Also made serial mavlink periodically send RC channel data every 100ms
2023-09-16 Some RC cleanup
    Created separate function to scale channel data for each RC
    protocol handler
2023-09-16 Fixed some compilation warnings
2023-09-16 Added USB connect state
2023-09-16 Added mavlink test motor throttle
    This can be very useful if you want to test the motors from a GUI.
    I'm not 100% sure that I'm treating the MAV_CMD_DO_MOTOR_TEST
    command as expected, but atm it simply force-sets the throttle of the
    given motor. Once this has been called, asac will never arm normally
    until rebooted, since the force-arm flag has been set.
2023-09-16 Added minor comment to clear up PCB mistake
2023-09-16 Fixed incorrect motor PWM pulse length
2023-09-16 Fixed bug with old reference to rx_protocol
2023-09-16 Added compile flag to remove warning
    The generated code from mavlink causes compilation warnings.
    These are known and mentioned in the mavlink docs.
    This commit adds the `-Wno-address-of-packed-member` flag to suppress
    these warnings, which hopefully won't do any harm
2023-09-16 Changed mavlink params -> settings
    The idea is that modules should use the settings variable, instead of the
    mavlink parameters.
    Even though they are the same thing, I think the separation makes sense.
2023-09-16 Added mavlink reset param command
2023-09-16 Fixed multicore write flash bug
    It seems like we need extra care when writing to flash on
    the second core.
    This commit adds some stuff that should but the primary core
    in a blocked state, before writing to flash.
    Hopefully this will work fine.
2023-09-16 Minor cleanup
    - Removed unnecessary function
    - Fixed bug when printing mavlink statustext, since the method
    expects a char buffer of size 50.
    - Added extra debug print info when writing to flash
2023-09-19 Fixed vbat ADC
    The ADC seems to be lagging so might need to check the filtering
    and software settings for this.
2023-09-19 Added mavlink battery status message
2025-09-26 Big refactor towards supporting different HALs
    Compiles OK
2025-09-26 Can build for different platforms now, great!
2025-09-27 Fixed sitl hal tcp sending
2025-09-27 Some cleanup Also changed system and component id to 1
2025-09-27 Some cleanup
2025-09-27 Started on abstraction of IMU
2025-09-27 Made tool to generate parameter description, from source code
2025-09-28 Rename build.py to run
    Added upload command for rp2040
2025-09-28 Better IMU abstraction
2025-09-28 cleanup
2025-09-28 Further HAL cleanup & refactoring
2025-09-28 Removed exposed variables
    Not sure exactly how I want to handle this tbh
2025-09-28 Made initial first draft idea of board yaml
2025-09-29 Added more functions for ringbuffers
    Will need to use these everywhere so must be efficient!
    Remains some tests for these to ensure they work proper and bug-free
2025-09-29 led cleanup
2025-09-29 Util: Added simple lpf
2025-09-29 Param: Added some missing parameters for the updated hal
2025-09-29 Documents: Added pico pinout image
2025-09-29 Tools: Keep track of last heartbeat in mav monitor
2025-09-30 HAL: Rewrite sitl serial hal
    Instead of relying on chatgpt generated code I re-wrote it instead to better understand it
    Quite rough but rx/tx seems to work OK
2025-09-30 HAL: Dummy sitl gpio
2025-09-30 Tests: Tried Unity testing framework
    Seems to work OK, let's see how it is to use.
    When building for SITL we also build tests.
    Run with `make test`
2025-09-30 HAL: Serial update all buses instead of single
    Same thing goes for i2c and spi!
2025-09-30 Nit: constrain instead of constrainf
2025-09-30 Mavlink: Write to stdout when gcs_printf in sitl
2025-10-01 Bat: Separated battery adc to backend and frontend
2025-10-03 AHRS: Created ahrs module, which will hade attitude estimation
2025-10-03 Battery: Fixed double header defguard
2025-10-03 Battery: Added frontend init method
    Clearer separation between frontend and backend.
    This way we can have different battery backends, similar to how AP has different battery monitor types
2025-10-03 Params: Added more params
2025-10-03 RC: Cleanup and refactor
2025-10-03 Main: Cleanup and refactor
2025-10-03 Build: Added missing source code to cmake
2025-10-03 Build: Include all modules
2025-10-03 Bug: Fixed I-term assignment
    Didn't even give it a value before...!
2025-10-03 Pid: Minor cleanup
2025-10-03 Bug: Added missing include
2025-10-04 I2C: Cleanup & initial rp2040 implementation
2025-10-04 SPI: Minor cleanup
2025-10-04 Bug: Fixed wrong includes
2025-10-04 HAL: Added params reading for rp2040
2025-10-04 Params: Improved param initialization
    More stable and some cleanup
    TODO: Still need to check CRC
2025-10-04 Build: Added imu mpu6500
2025-10-04 Flash: Change default flash size to 2MB
    NOTE: This should not be in hal_flash.c but in board-specific build!!
2025-10-04 Flash: Added write method for rp2040
2025-10-04 Hal: Changed name of reboot
2025-10-04 Cleanup: Removed unused old code
2025-10-04 Hal: Bug: Don't send/read data if USB isn't connected
2025-10-04 Hal: Cleanup: Removed unused code
2025-10-04 Hal: Bug: Prevent i2c/spi init with bad params
2025-10-04 Scheduler: Bug: Prevent scheduler ever sleeping for more than period time
    If there would be some kind of overflow/bug this clamping should be nice
2025-10-04 Hal: busy-wait sleep instead of sleep_xx
    the sleep_xx seems to screw the debugger for some reason...
    It gets stuck when using sleep_ms()
2025-10-04 Hal: Debugger stuck fix
2025-10-04 Mavlink: Added command to scan i2c bus
2025-10-04 Main: Some refactor to run
2025-10-04 Hal: Bug: initialized same i2c bus twice...
2025-10-04 Hal: Bug: i2c bus probing took wrong i2c bus
2025-10-05 IMU: Proper init - Can boot without proper IMU selection
2025-10-05 Hal: Some refactor
2025-10-05 Hal: Added helper to get serial port configured for a given protocol
2025-10-05 Imu: Refactor & cleanup
2025-10-05 Hal: Adopt mpu6050 to new HAL. Got it working to get data :)
2025-10-05 RC: Initial empty code of mavlink backend
2025-10-05 Mavlink: Bug: Fixed old code ref
2025-10-05 Controller: Removed rc reading / filter from control loop
    This will be handle by rc_update() instead
2025-10-05 Build: Updated run script
2025-10-05 Sensor: Added sensor struct for health/enabled etc Useful for mavlink system status packet
2025-10-05 State: Added some states & moved flightmode_t into state.h
2025-10-05 Imu: Created function to apply ahrs orientation to reading
2025-10-05 Imu: Cleanup & refactor
2025-10-14 Motor: Cleanup & use new HAL instead of old code
2025-10-14 RC: Added protocl and handler for mavlink backend
2025-10-14 HAL: Separate PWM files with intiial rp2040 implementation
2025-10-14 Controll: Trhottle control take input 0-1
2025-10-14 MAVLink: Added subscribe function for handling rc channels override message
2025-10-14 Params: Added missing parameters
2025-10-14 IMU: More stable initialization
2025-10-14 IMU: Dummy sitl values for imu reading
2025-10-14 Build: added hal pwm

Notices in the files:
parts and their libraries:
Copyright 2016 Accelerated Designs. All rights reserved.
